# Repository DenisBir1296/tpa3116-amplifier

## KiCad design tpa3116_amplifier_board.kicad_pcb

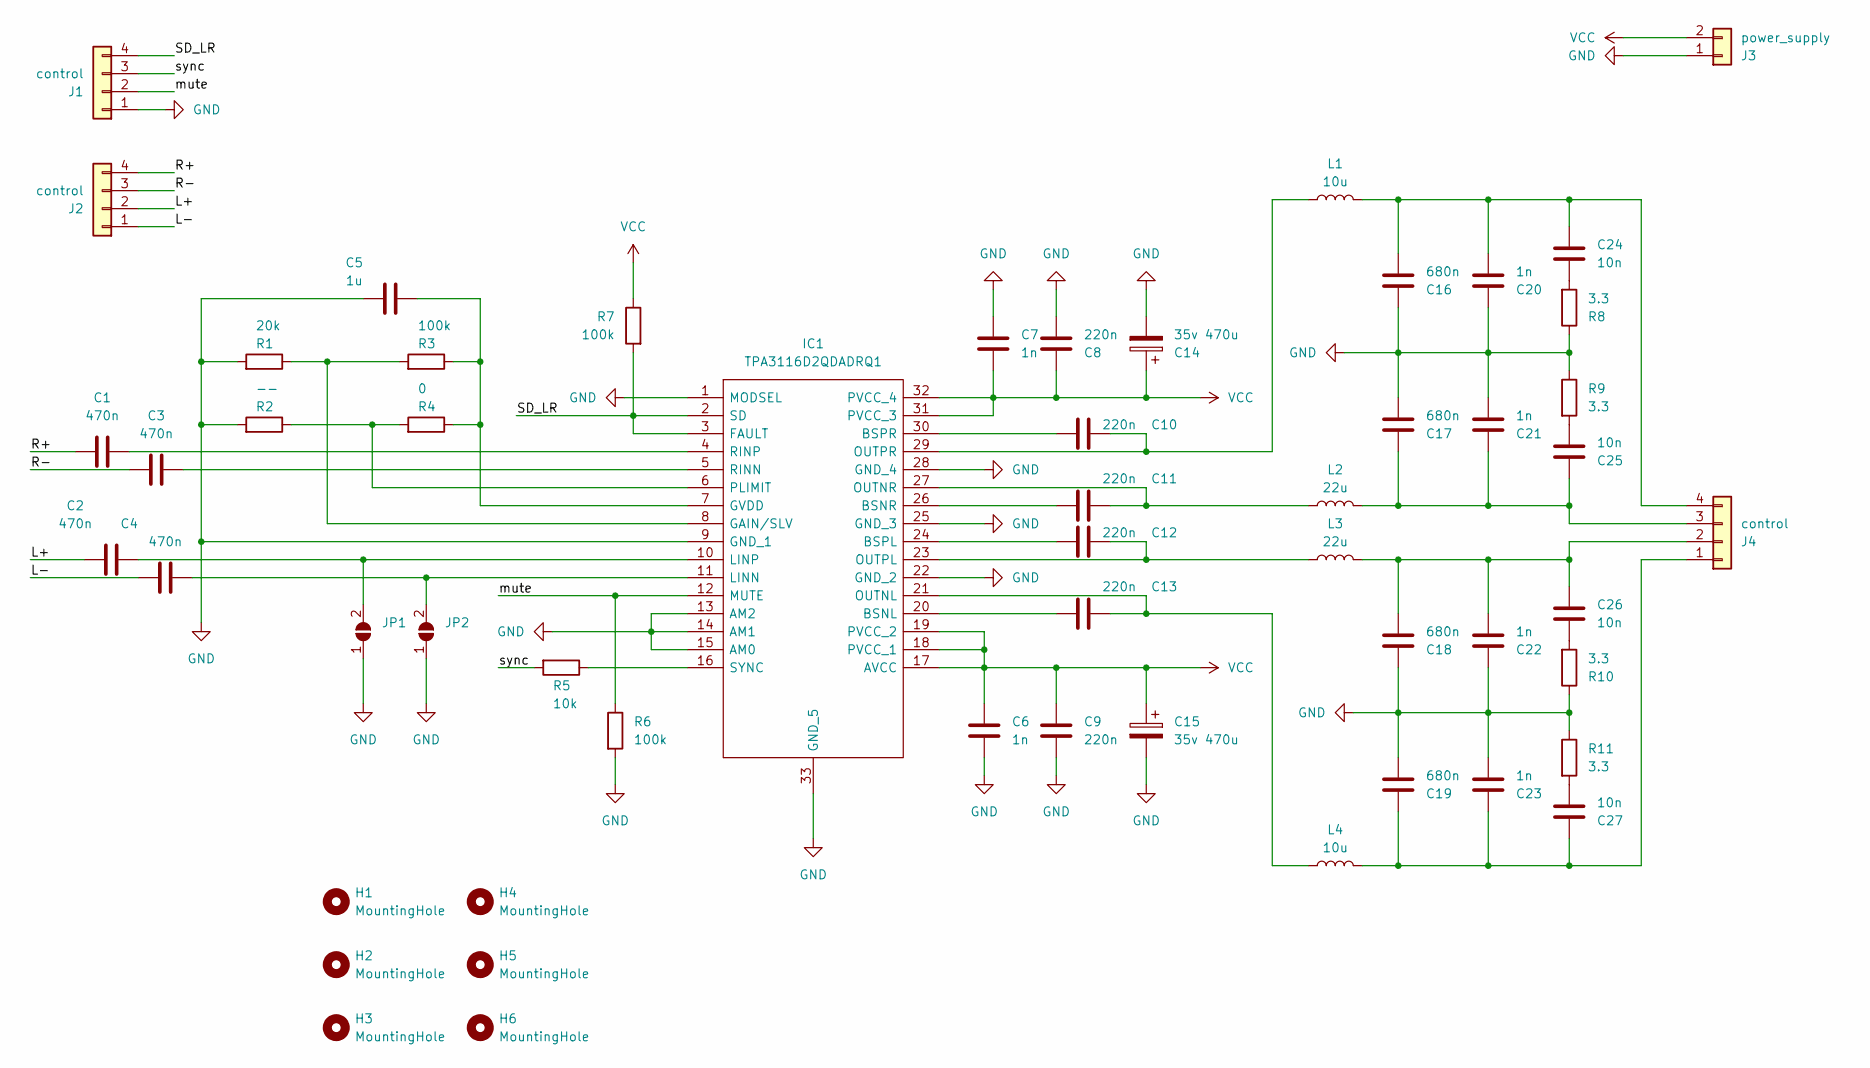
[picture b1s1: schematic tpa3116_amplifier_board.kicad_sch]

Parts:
C1, C2, C3, C4: 470n; C_Rect_L7.0mm_W4.5mm_P5.00mm
C5: 1u; C_0805_2012Metric
C6, C7, C20, C21, C22, C23: 1n; C_0603_1608Metric
C8, C9, C10, C11, C12, C13: 220n; C_0603_1608Metric
C14, C15: 35v 470u; CP_Radial_D10.0mm_P5.00mm
C16, C17, C18, C19: 680n; C_Rect_L7.0mm_W4.5mm_P5.00mm
C24, C25, C26, C27: 10n; C_0603_1608Metric
H1, H2, H3, H4, H5, H6: MountingHole; MountingHole_3.2mm_M3_DIN965_Pad
IC1: TPA3116D2QDADRQ1; SOP65P810X120-33N; Manufacturer_Part_Number TPA3116D2QDADRQ1; Mouser Part Number 595-TPA3116D2QDADRQ1
J1, J2: control; JST_EH_B4B-EH-A_1x04_P2.50mm_Vertical
J3: power_supply; JST_VH_B2P-VH-B_1x02_P3.96mm_Vertical
J4: control; JST_VH_B4P-VH-B_1x04_P3.96mm_Vertical
JP1, JP2: SolderJumper_2_Open; SolderJumper-2_P1.3mm_Open_RoundedPad1.0x1.5mm
L1, L4: 10u; L_12x12mm_H8mm
L2, L3: 22u; L_12x12mm_H8mm
R1: 20k; R_0603_1608Metric
R2: --; R_0603_1608Metric
R3, R6, R7: 100k; R_0603_1608Metric
R4: 0; R_0603_1608Metric
R5: 10k; R_0603_1608Metric
R8, R9, R10, R11: 3.3; R_0603_1608Metric

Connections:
/L+: C2.1, J2.2
/L-: C4.1, J2.1
/R+: C1.1, J2.4
/R-: C3.1, J2.3
/SD_LR: IC1.2 (SD), IC1.3 (FAULT), J1.4, R7.2
/mute: IC1.12 (MUTE), J1.2, R6.1
/sync: J1.3, R5.2
GND: C5.1, C6.2, C7.1, C8.2, C9.2, C14.2, C15.2, C16.1, C17.2, C18.1, C19.2, C20.1, C21.2, C22.1, C23.2, IC1.1 (MODSEL), IC1.9 (GND_1), IC1.13 (AM2), IC1.14 (AM1), IC1.15 (AM0), IC1.22 (GND_2), IC1.25 (GND_3), IC1.28 (GND_4), IC1.33 (GND_5), J1.1, J3.1, JP1.1 (A), JP2.1 (A), R1.2, R2.2, R6.2, R8.1, R9.1, R10.1, R11.1
unnamed: C24.2, R8.2
unnamed: C25.2, R9.2
unnamed: C26.2, R10.2
unnamed: C27.2, R11.2
unnamed: C13.2, IC1.20 (BSNL)
unnamed: C11.2, IC1.26 (BSNR)
unnamed: C12.2, IC1.24 (BSPL)
unnamed: C10.2, IC1.30 (BSPR)
unnamed: IC1.8 (GAIN/SLV), R1.1, R3.2
unnamed: C5.2, IC1.7 (GVDD), R3.1, R4.1
unnamed: C4.2, IC1.11 (LINN), JP2.2 (B)
unnamed: C2.2, IC1.10 (LINP), JP1.2 (B)
unnamed: C13.1, IC1.21 (OUTNL), L4.1
unnamed: C11.1, IC1.27 (OUTNR), L2.1
unnamed: C12.1, IC1.23 (OUTPL), L3.1
unnamed: C10.1, IC1.29 (OUTPR), L1.1
unnamed: IC1.6 (PLIMIT), R2.1, R4.2
unnamed: C3.2, IC1.5 (RINN)
unnamed: C1.2, IC1.4 (RINP)
unnamed: IC1.16 (SYNC), R5.1
unnamed: C19.1, C23.1, C27.1, J4.1, L4.2
unnamed: C18.2, C22.2, C26.1, J4.2, L3.2
unnamed: C17.1, C21.1, C25.1, J4.3, L2.2
unnamed: C16.2, C20.2, C24.1, J4.4, L1.2
VCC: C6.1, C7.2, C8.1, C9.1, C14.1, C15.1, IC1.17 (AVCC), IC1.18 (PVCC_1), IC1.19 (PVCC_2), IC1.31 (PVCC_3), IC1.32 (PVCC_4), J3.2, R7.1

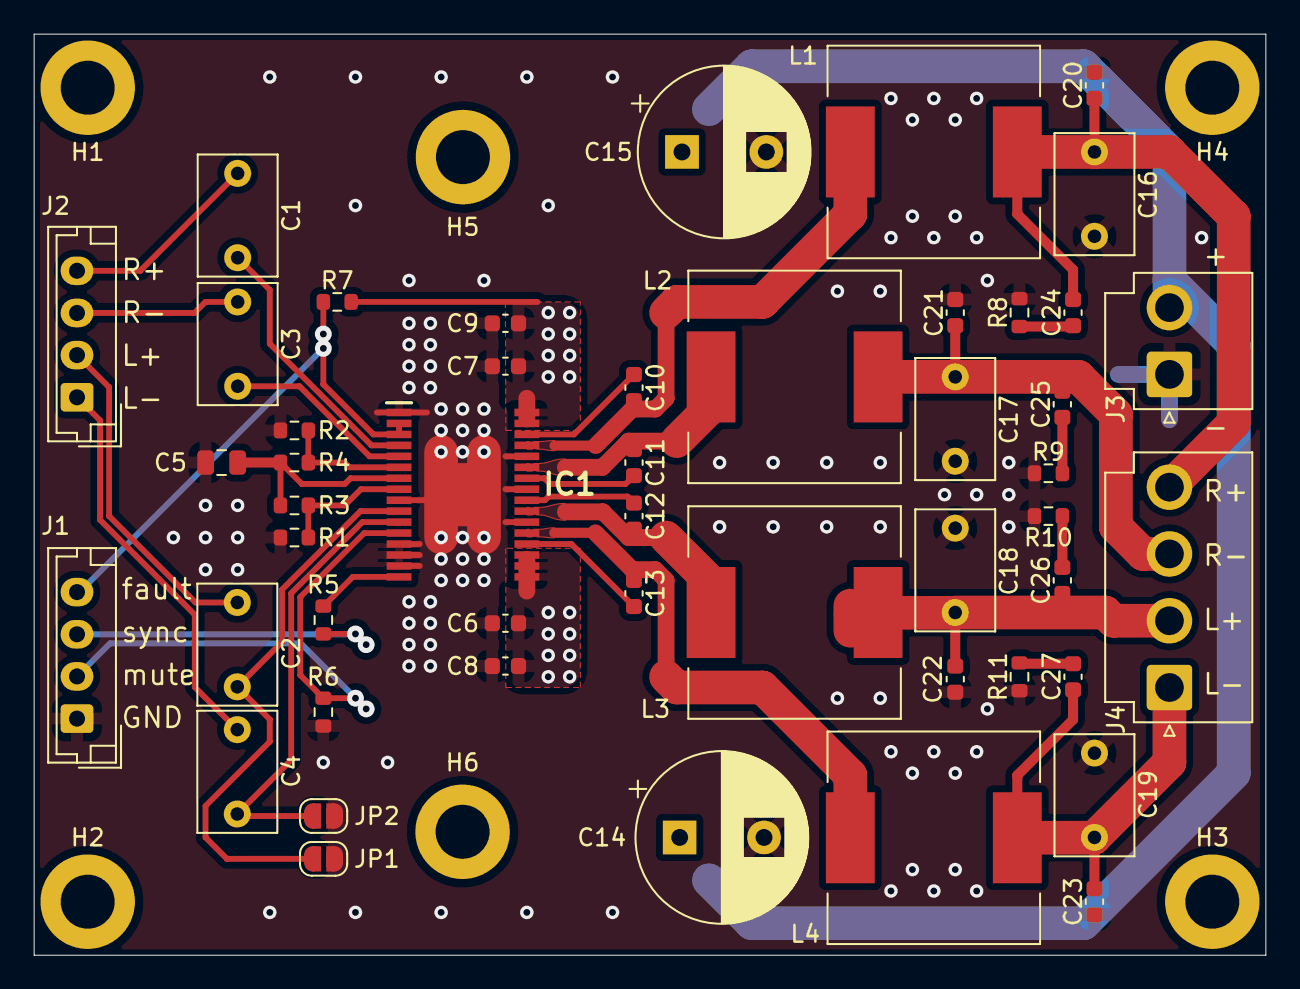
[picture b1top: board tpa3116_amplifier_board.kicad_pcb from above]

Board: 2 copper layers, 73.0 x 54.6 mm, 55 parts (0 on the bottom side), 33 nets.

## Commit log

2025-07-16 Завершенная плата, осталось надписи подправить
2025-07-16 Добавил надписи
2025-07-16 Добавил картинку
2025-07-17 Переделал в pbtl версию
2025-07-17 Закрыл kicad
2025-07-17 Надпись подправил
2025-07-17 Сформировал gerber файлы и добавил изображение
2025-07-17 Сформировал gerber файлы
2025-07-17 Удалил архив со старыми gerber
2025-07-18 Заменил пленочные выводные конденсаторы в фильтре на SMD
2025-07-18 Изображение обновил и gerber
2025-07-18 Изображение обновил
2025-07-20 Уменьшил размер платы
2025-07-20 Уменьшил размер коннекторов и подправил переходные отверстия
2025-07-21 Небольшие правки
2025-07-26 переделал на разъемы
2025-07-26 мелкие правки
2025-07-26 поправил дорожки питания
2025-08-03 изменил расположение разъемов и уменьшил размер платы
2025-08-03 исправил ошибку в схеме
2025-08-03 исправил ошибку в схеме, добавил разъемы
2025-08-03 Обновил изображение
